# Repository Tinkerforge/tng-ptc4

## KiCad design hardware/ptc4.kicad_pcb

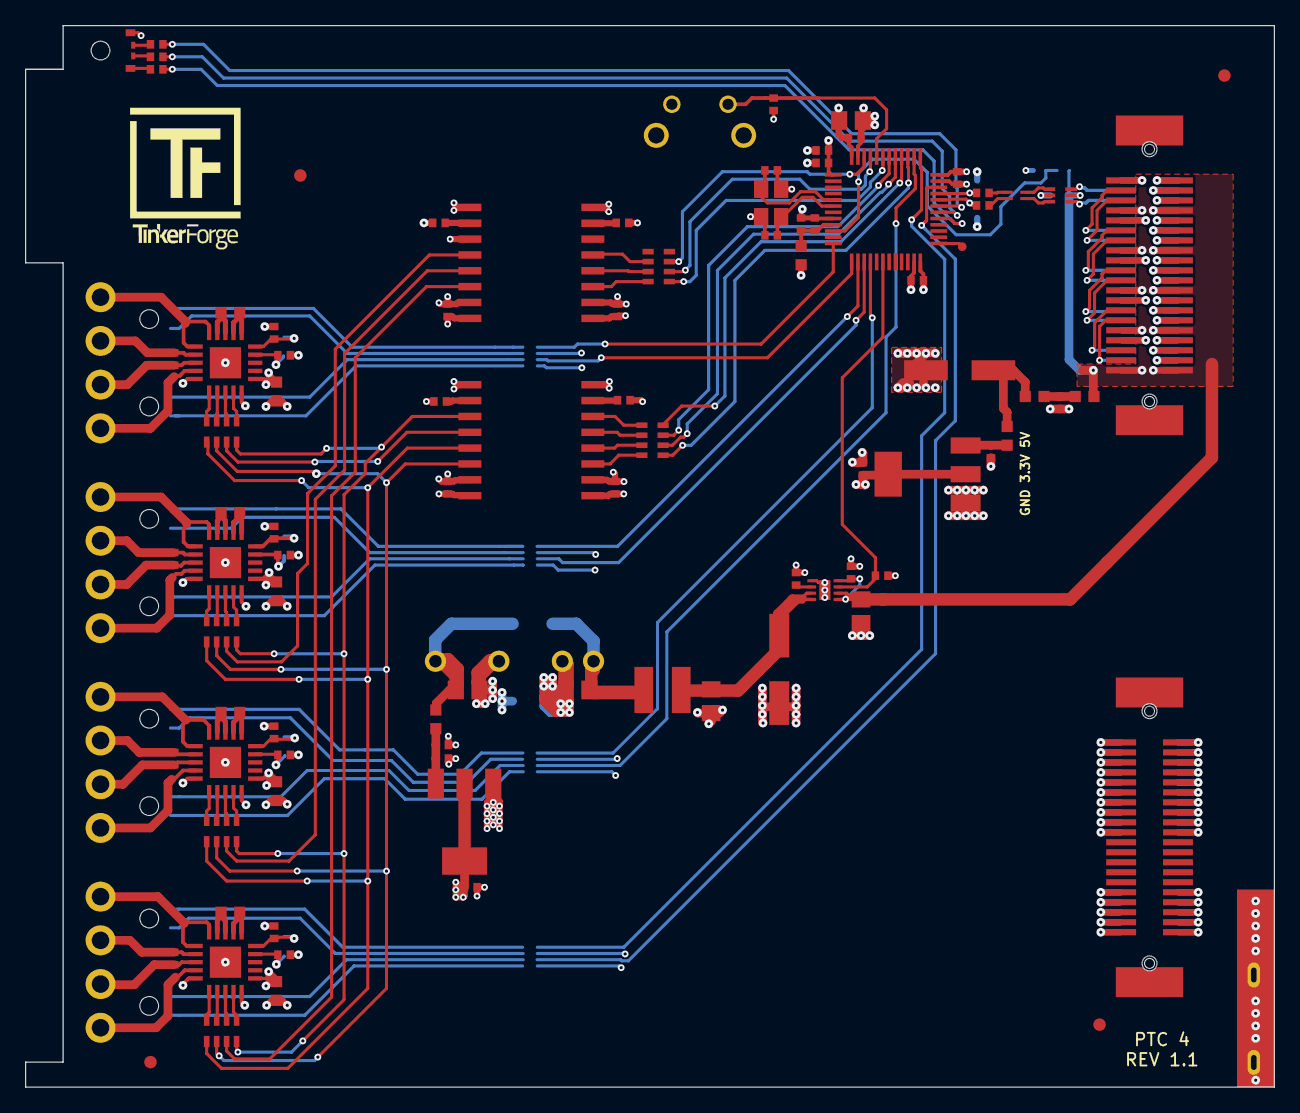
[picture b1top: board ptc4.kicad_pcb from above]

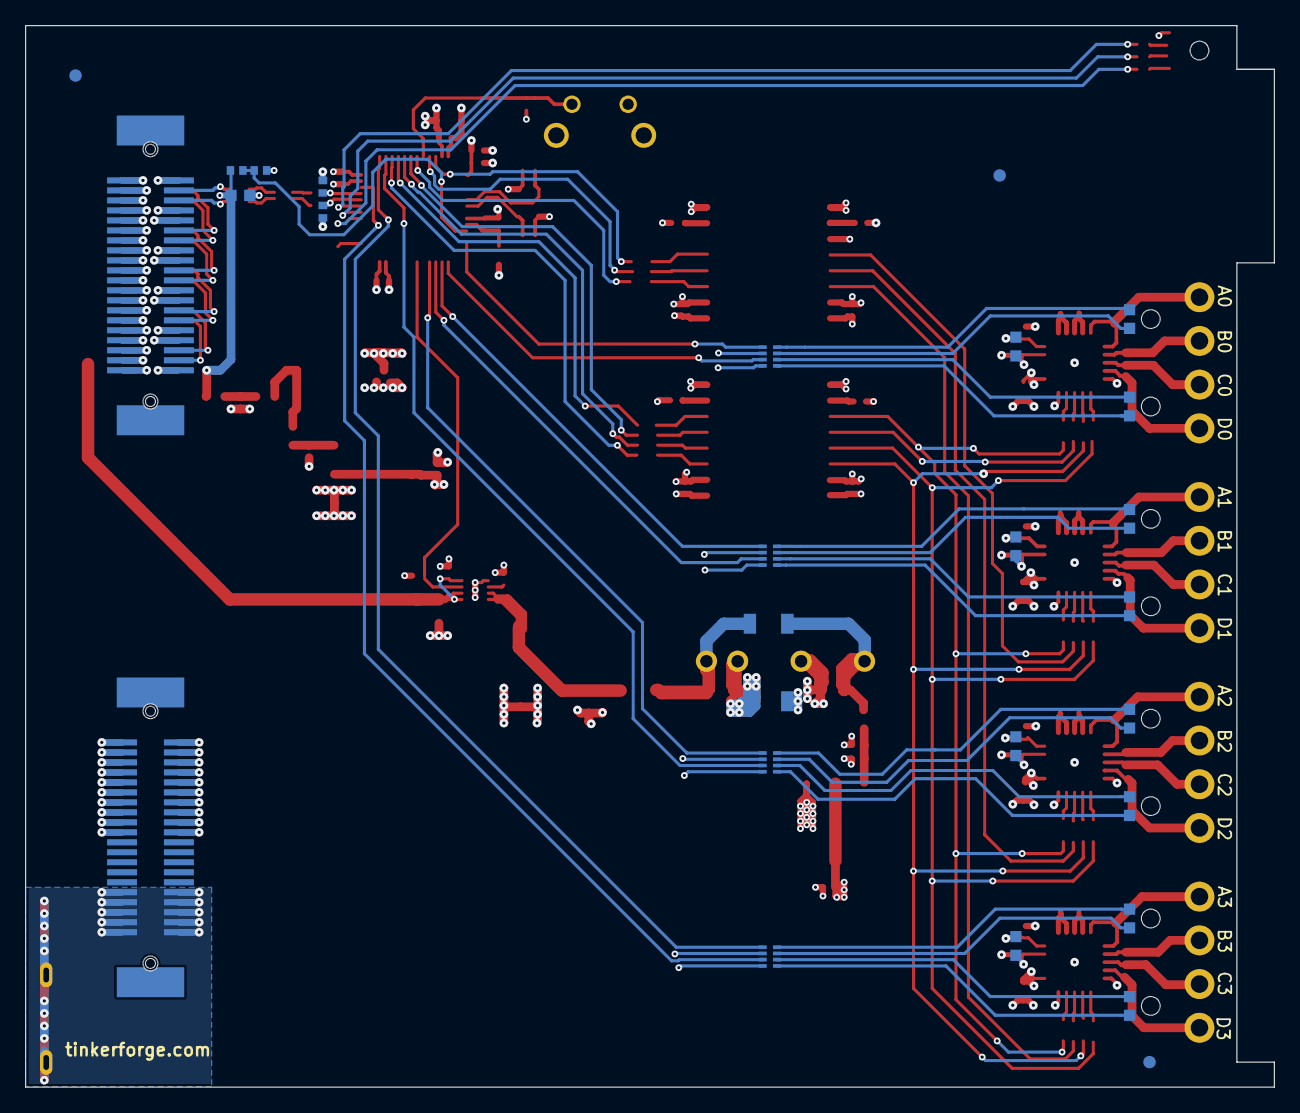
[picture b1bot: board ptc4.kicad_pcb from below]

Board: 4 copper layers, 100.0 x 85.0 mm, 127 parts (28 on the bottom side), 142 nets.

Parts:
C101, C102, C116, C117, C118, C217, C218: 1uF; C0402F
C103, C104, C105, C106, C107, C112, C201, C202, C203, C204, C205, C206, C207, C208, C209, C210, C211, C212, C213, C214, C215, C216, C219: 100nF; C0402F
C108, C109: 33pF; C0402F
C110: 10uF; C0805E
C111, C120: 100uF; ELKO_63
C113, C114: 47pF; C0402F
C115: 2.2uF; C0603F
C119: DNP; C0402F
C121, C122, C123, C126: 4.7uF/16V; C0805E
D203, D204, D205, D206, D207, D208, D209, D210: LED; LED-LP
Fiducial_Mark: VAL**; Fiducial_Mark
Fiducial_Mark#2, Fiducial_Mark#3, Fiducial_Mark#4, Fiducial_Mark#5, Fiducial_Mark#6, Fiducial_Mark#7: VAL**; Fiducial_Mark
J101: TNG-Power-TOP; TNG-40-TOP
J102: TNG-Power-BTM; TNG-40-BTM
J103: TNG-Data-TOP; TNG-40-TOP
J104: TNG-Data-BTM; TNG-40-BTM
L101, L201, L202, L203, L204, L205, L206, L207, L208: FB; R0603F
L102, L103, L104, L209: INDUCTs; R0603F
L105: 744230900; WE-CNSW-0603
L106: 6.8uH; NR4040
LED101: EASV3015RGBA0; LED-RGB-LP
P102: Debug; DEBUG_PAD
P103: PE; PE_Hook
P201: INPUT0; OQ_4P
P202: INPUT1; OQ_4P
P203: INPUT2; OQ_4P
P204: INPUT3; OQ_4P
R101, R107, R108: 1k; R0402F
R102, R105, R205, R206, R207, R208: 0; R0402F
R103, R104: 22; R0402F
R106: 56; R0402F
R109: 10k; R0402F
R110, R111: 0; R1206
R201, R202, R203, R204: 390/3900 0.1%; R0603F
RP201, RP202, RP203, RP204: 470; 4X0402
RP205, RP206, RP207, RP208, RP209, RP210: 180; 4X0603
SW101: BOOT; TACT-6MM-HOR
U101: STM32F070CBT6; LQFP48
U102, U207: AZ1117EH; SOT-223
U103: 82400152; SOT563-SPEC
U104: TPS22975; WSON8-2x2
U105: DNP; SIP7
U201, U202, U203, U204: MAX31865; QFN-20-5x5
U205, U206: ISO7741DWR; SOIC16_WIDE
X101: 8MHz; CRYSTAL_3225

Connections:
3V3: C101.1, C103.1, C104.1, C105.1, C106.1, C110.1, C116.1, C215.1, C216.1, L101.1, LED101.1, R207.1, R208.1, RP201.2, RP201.4, RP202.2, RP202.4, RP203.2, RP203.4, RP204.2, RP204.4, SW101.1, U101.1, U101.24, U101.36, U101.48, U102.2, U205.1, U206.1
5V-ENABLE: R109.1, U101.18, U104.3
5VA: C115.1, C118.1, C123.1, J103.7, J103.8, J103.15, J103.16, J103.23, J103.24, J103.31, J103.32, J103.39, J103.40, J104.7, J104.8, J104.15, J104.16, J104.23, J104.24, J104.31, J104.32, J104.39, J104.40, L104.1, R107.1, U103.5, U104.1, U104.2, U104.4
+5V: C111.1, L102.1, L103.2
A3V3: C207.1, C208.1, C209.1, C212.1, C213.1, C214.1, C217.1, L203.2, L204.2, L206.2, L208.2, R205.2, R206.2, U201.19, U202.19, U203.19, U204.19, U205.16, U206.16, U207.2
A5V: C122.1, L209.1, R110.1, U105.6
AGND: C122.2, C207.2, C208.2, C209.2, C212.2, C213.2, C214.2, C217.2, C218.2, C219.2, L201.2, L202.2, L205.2, L207.2, R111.1, U105.4, U201.15, U202.15, U203.15, U204.15, U205.9, U205.15, U206.9, U206.11, U206.15, U207.1
AGND1: C204.2, L201.1, U201.10, U201.16, U201.EP
AGND2: C205.2, L202.1, U202.10, U202.16, U202.EP
AGND3: C206.2, L205.1, U203.10, U203.16, U203.EP
AGND4: C211.2, L207.1, U204.10, U204.16, U204.EP
AGNDA: J101.2, J101.4, J101.6, J101.8, J101.10, J101.12, J101.14, J101.16, J101.18, J101.20, J102.1, J102.3, J102.5, J102.7, J102.9, J102.11, J102.13, J102.15, J102.17, J102.19
AIN0: R107.2, R108.1, U101.10
CS0: RP205.6, U205.12
CS1: RP206.6, U206.12
CS2: RP207.6, U206.13
CS3: RP208.6, U206.14
Earth: J101.31, J101.32, J101.33, J101.34, J101.35, J101.36, J101.37, J101.38, J101.39, J101.40, J102.31, J102.32, J102.33, J102.34, J102.35, J102.36, J102.37, J102.38, J102.39, J102.40, P103.1
GND: C101.2, C102.2, C103.2, C104.2, C105.2, C106.2, C107.2, C108.1, C109.1, C110.2, C111.2, C112.2, C113.2, C114.2, C115.2, C116.2, C117.2, C118.2, C119.1, C120.2, C121.2, C123.2, C126.2, C215.2, C216.2, J103.1, J103.2, J103.4, J103.6, J103.9, J103.10, J103.12, J103.14, J103.17, J103.18, J103.20, J103.22, J103.25, J103.26, J103.28, J103.30, J103.33, J103.34, J103.36, J103.38, J104.1, J104.2, J104.3, J104.5, J104.9, J104.10, J104.11, J104.13, J104.17, J104.18, J104.19, J104.21, J104.25, J104.26, J104.27, J104.29, J104.33, J104.34, J104.35, J104.37, R101.1, R108.2, R109.2, R111.2, U101.8, U101.23, U101.35, U101.47, U102.1, U103.2, U104.5, U104.EXP, U105.2, U205.2, U205.8, U206.2, U206.8, X101.3
LED0: RP201.1, U101.12
LED1: RP201.3, U101.13
LED2: RP202.1, U101.14
LED3: RP202.3, U101.15
LED4: RP203.1, U101.16
LED5: RP203.3, U101.38
LED6: RP204.1, U101.37
LED7: RP204.3, U101.34
LEDB: R106.1, U101.31
LEDG: R105.1, U101.30
LEDR: R102.1, U101.29
unnamed: C102.1, C107.1, L101.2, U101.9
unnamed: C108.2, U101.5, X101.2
unnamed: C109.2, U101.6, X101.1
unnamed: C112.1, L103.1, L104.2
unnamed: C117.1, L102.2, U102.3
unnamed: C119.2, U104.6
unnamed: C120.1, C126.1, L106.1, U104.7, U104.8
unnamed: C121.1, L106.2, R110.2, U105.1
unnamed: C201.1, P201.2, U201.7
unnamed: C201.2, P201.3, U201.8
unnamed: C202.1, P202.2, U202.7
unnamed: C202.2, P202.3, U202.8
unnamed: C203.1, P203.2, U203.7
unnamed: C203.2, P203.3, U203.8
unnamed: C204.1, L203.1, U201.20
unnamed: C205.1, L204.1, U202.20
unnamed: C206.1, L206.1, U203.20
unnamed: C210.1, P204.2, U204.7
unnamed: C210.2, P204.3, U204.8
unnamed: C211.1, L208.1, U204.20
unnamed: C218.1, C219.1, L209.2, U207.3
unnamed: D203.1, RP201.7
unnamed: D203.2, RP201.8
unnamed: D204.1, RP201.5
unnamed: D204.2, RP201.6
unnamed: D205.1, RP202.7
unnamed: D205.2, RP202.8
unnamed: D206.1, RP202.5
unnamed: D206.2, RP202.6
unnamed: D207.1, RP203.7
unnamed: D207.2, RP203.8
unnamed: D208.1, RP203.5
unnamed: D208.2, RP203.6
unnamed: D209.1, RP204.7
unnamed: D209.2, RP204.8
unnamed: D210.1, RP204.5
unnamed: D210.2, RP204.6
unnamed: J103.3, J104.12
unnamed: J103.5, J104.14
unnamed: J103.11, J104.20
unnamed: J103.13, J104.22
unnamed: J103.19, J104.28
unnamed: J103.21, J104.30
unnamed: J103.27, J104.36
unnamed: J103.29, J104.38
unnamed: LED101.2, R106.2
unnamed: LED101.3, R105.2
unnamed: LED101.4, R102.2
unnamed: P102.1, U101.25
unnamed: P201.1, U201.5, U201.6
unnamed: P201.4, U201.9
unnamed: P202.1, U202.5, U202.6
unnamed: P202.4, U202.9
unnamed: P203.1, U203.5, U203.6
unnamed: P203.4, U203.9
unnamed: P204.1, U204.5, U204.6
unnamed: P204.4, U204.9
unnamed: R101.2, SW101.2, U101.44
unnamed: R201.1, U201.3, U201.4
unnamed: R201.2, U201.1, U201.2
unnamed: R202.1, U202.3, U202.4
unnamed: R202.2, U202.1, U202.2
unnamed: R203.1, U203.3, U203.4
unnamed: R203.2, U203.1, U203.2
unnamed: R204.1, U204.3, U204.4
unnamed: R204.2, U204.1, U204.2
unnamed: R205.1, U205.10
unnamed: R206.1, U206.10
unnamed: R207.2, U205.7
unnamed: R208.2, U206.7
unnamed: RP205.1, U201.11
unnamed: RP205.2, U201.12
unnamed: RP205.3, U201.13
unnamed: RP205.4, U201.14
unnamed: RP206.1, U202.11
unnamed: RP206.2, U202.12
unnamed: RP206.3, U202.13
unnamed: RP206.4, U202.14
unnamed: RP207.1, U203.11
unnamed: RP207.2, U203.12
unnamed: RP207.3, U203.13
unnamed: RP207.4, U203.14
unnamed: RP208.1, U204.11
unnamed: RP208.2, U204.12
unnamed: RP208.3, U204.13
unnamed: RP208.4, U204.14
unnamed: RP209.1, U205.3
unnamed: RP209.2, U205.4
unnamed: RP209.3, U205.5
unnamed: RP209.4, U205.6
unnamed: RP210.1, U206.3
unnamed: RP210.2, U206.4
unnamed: RP210.3, U206.5
SCLK: RP205.7, RP206.7, RP207.7, RP208.7, U205.14
SDI: RP205.8, RP206.8, RP207.8, RP208.8, U205.13
SDO: RP205.5, RP206.5, RP207.5, RP208.5, U205.11
SPI-CLK: RP209.8, U101.39
SPI-CS0: RP209.6, U101.42
SPI-CS1: RP210.6, U101.46
SPI-CS2: RP210.7, U101.45
SPI-CS3: RP210.8, U101.43
SPI-MISO: RP209.5, U101.40
SPI-MOSI: RP209.7, U101.41
USB-DM: C114.1, R104.2, U101.32
USB-DMA: J104.6, U103.4
USB-DMB: L105.1, U103.3
USB-DMC: L105.2, R104.1
USB-DP: C113.1, R103.2, U101.33
USB-DPA: J104.4, U103.6
USB-DPB: L105.4, U103.1
USB-DPC: L105.3, R103.1
VCCPWRA: J101.1, J101.3, J101.5, J101.7, J101.9, J101.11, J101.13, J101.15, J101.17, J101.19, J102.2, J102.4, J102.6, J102.8, J102.10, J102.12, J102.14, J102.16, J102.18, J102.20

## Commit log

2020-08-31 add first draft
2020-09-03 rename
2020-09-04 add version 1.1
    fix footprints
2020-09-07 fix values
2020-09-07 fix footprint
2020-09-08 all footprints updated
2020-09-09 default is non isolated
2020-09-10 fix 3d stuff

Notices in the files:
hardware/ptc4.kicad_pcb:
Licensed under CERN OHL v.1.1
Copyright (©) 2020, B.Nordmeyer
Copyright Tinkerforge GmbH 2020.
This documentation describes Open Hardware and is licensed under the
CERN OHL v. 1.1.
